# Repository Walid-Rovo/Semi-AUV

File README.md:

Welcome to the repository of Semi-AUV by Amgad Ehab, Walid Ismail. A Senior Project in the Arab Academy for Science & Technology under the supervision of Dr Shady A. Maged.

This repository will include all aspects of developing a semi-autonomous underwater vehicle for marine robotics research and educational purposes.

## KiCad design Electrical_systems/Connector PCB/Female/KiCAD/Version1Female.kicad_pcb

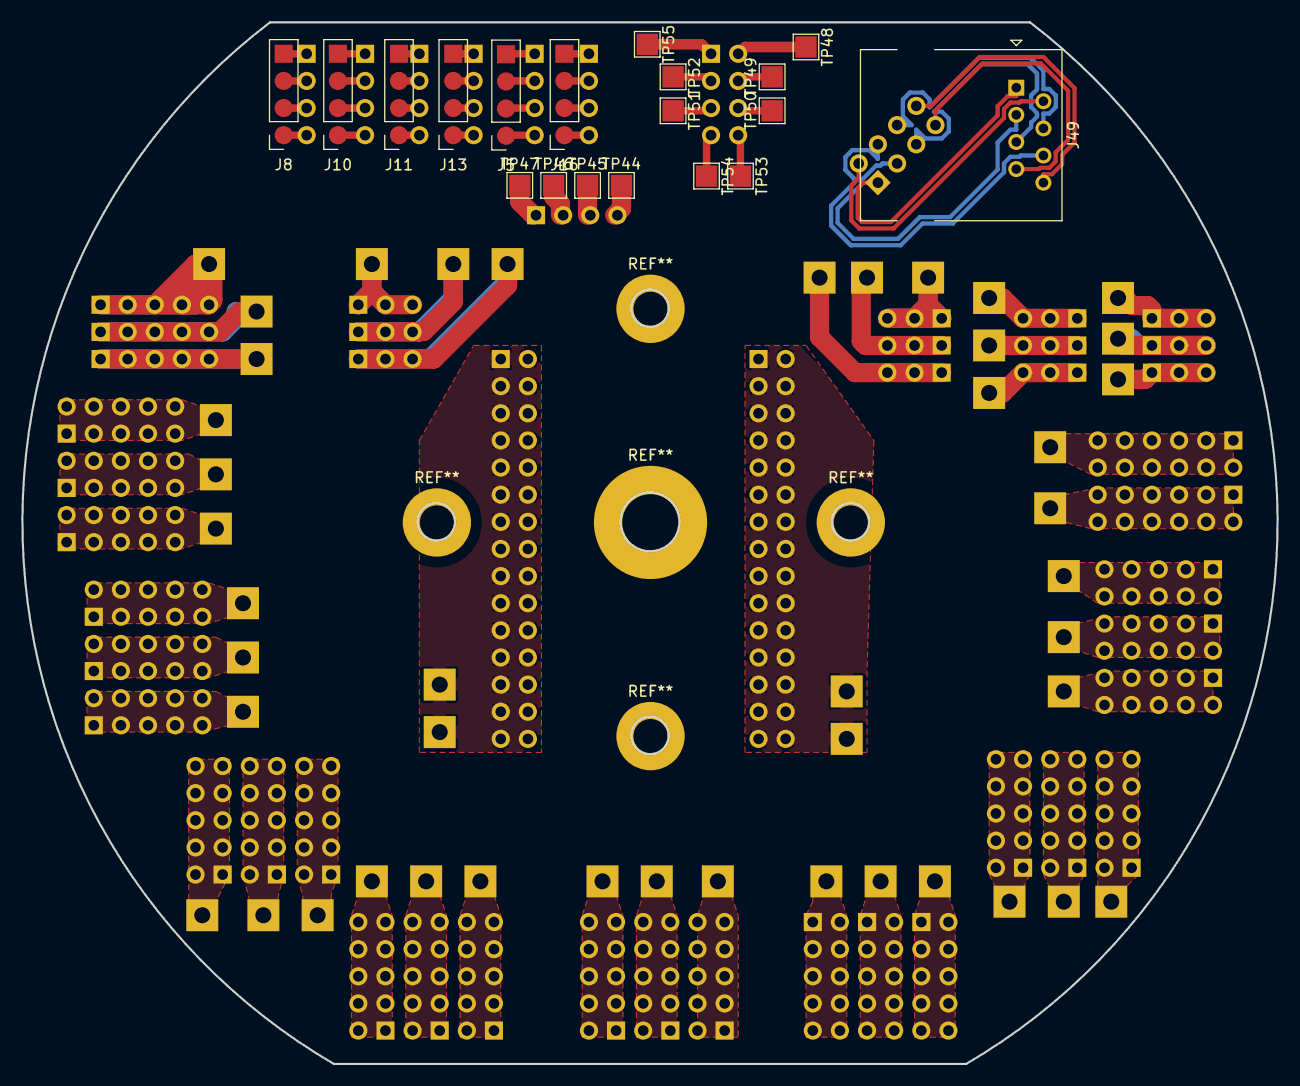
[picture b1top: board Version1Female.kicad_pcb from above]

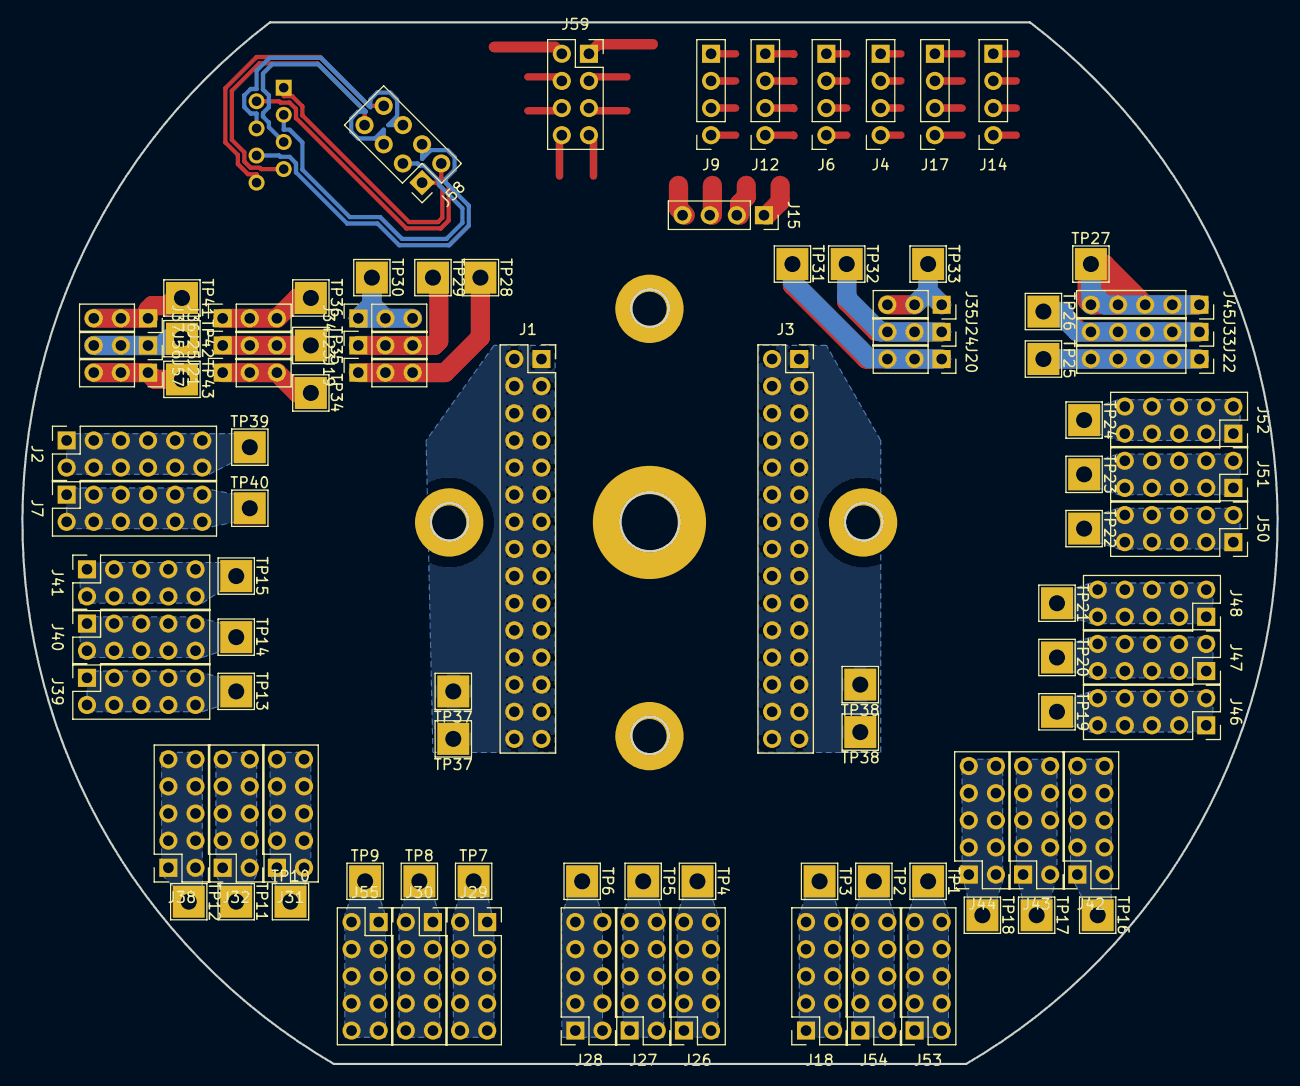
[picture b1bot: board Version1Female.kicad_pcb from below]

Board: 2 copper layers, 117.5 x 97.5 mm, 116 parts (97 on the bottom side), 79 nets.

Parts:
J1, J3: Conn_01x30_Male; PinSocket_2x15_P2.54mm_Vertical
J2, J7: Conn_01x12_Male; PinSocket_2x06_P2.54mm_Vertical
J4, J5, J6, J8, J9, J10, J11, J12, J13, J14, J16, J17: Conn_01x04; PinSocket_1x04_P2.54mm_Vertical
J15: Conn_01x04_Male; PinSocket_1x04_P2.54mm_Vertical
J18, J26, J27, J28, J29, J30, J31, J32, J38, J39, J40, J41, J42, J43, J44, J46, J47, J48, J50, J51, J52, J53, J54, J55: Conn_01x10; PinSocket_2x05_P2.54mm_Vertical
J19, J20, J21, J23, J24, J25, J34, J35, J36, J37, J56, J57: Conn_01x03_Male; PinSocket_1x03_P2.54mm_Vertical
J22, J33, J45: Conn_01x05_Male; PinSocket_1x05_P2.54mm_Vertical
J49: 8P8C; RJ45_Ninigi_GE
J58, J59: Conn_01x08; PinSocket_2x04_P2.54mm_Vertical
TP1, TP2, TP3, TP4, TP5, TP6, TP7, TP8, TP9, TP10, TP11, TP12, TP13, TP14, TP15, TP16, TP17, TP18, TP19, TP20, TP21, TP22, TP23, TP24, TP25, TP26, TP27, TP28, TP29, TP30, TP31, TP32, TP33, TP34, TP35, TP36, TP37, TP37#2, TP38, TP38#2, TP39, TP40, TP41, TP42, TP43: TestPoint; TestPoint_THTPad_3.0x3.0mm_Drill1.5mm
TP44, TP45, TP46, TP47, TP48, TP49, TP50, TP51, TP52, TP53, TP54, TP55: TestPoint; TestPoint_Pad_2.0x2.0mm

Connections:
3V3: J15.2, TP46.1
+12_VB1: J2.1, J2.2, J2.3, J2.4, J2.5, J2.6, J2.7, J2.8, J2.9, J2.10, J2.11, J2.12, TP39.1
+48_VA: J1.1, J1.2, J1.3, J1.4, J1.5, J1.6, J1.7, J1.8, J1.9, J1.10, J1.11, J1.12, J1.13, J1.14, J1.15, J1.16, J1.17, J1.18, J1.19, J1.20, J1.21, J1.22, J1.23, J1.24, J1.25, J1.26, J1.27, J1.28, J1.29, J1.30, TP37.1, TP37#2.1
+M0: J22.1, J22.2, J22.3, J22.4, J22.5, TP25.1
+M1: J19.1, J19.2, J19.3, TP28.1
+M2: J20.1, J20.2, J20.3, TP31.1
+M3: J21.1, J21.2, J21.3, TP34.1
+M4: J37.1, J37.2, J37.3, TP41.1
-M0: J33.1, J33.2, J33.3, J33.4, J33.5, TP26.1
-M1: J23.1, J23.2, J23.3, TP29.1
-M2: J24.1, J24.2, J24.3, TP32.1
-M3: J25.1, J25.2, J25.3, TP35.1
-M4: J56.1, J56.2, J56.3, TP42.1
EthA+: J49.2, J58.2
EthA-: J49.1, J58.1
EthB+: J49.6, J58.4
EthB-: J49.3, J58.3
EthC+: J49.5, J58.5
EthC-: J49.4, J58.6
EthD+: J49.8, J58.8
EthD-: J49.7, J58.7
GND: J15.1, TP47.1, TP55.1
GND_VA: J3.1, J3.2, J3.3, J3.4, J3.5, J3.6, J3.7, J3.8, J3.9, J3.10, J3.11, J3.12, J3.13, J3.14, J3.15, J3.16, J3.17, J3.18, J3.19, J3.20, J3.21, J3.22, J3.23, J3.24, J3.25, J3.26, J3.27, J3.28, J3.29, J3.30, TP38.1, TP38#2.1
GND_VB1: J7.1, J7.2, J7.3, J7.4, J7.5, J7.6, J7.7, J7.8, J7.9, J7.10, J7.11, J7.12, TP40.1
RA1: J4.1, J11.1
RA2: J4.2, J11.2
RA3: J4.3, J11.3
RA4: J4.4, J11.4
RB1: J5.1, J12.1
RB2: J5.2, J12.2
RB3: J5.3, J12.3
RB4: J5.4, J12.4
RC1: J6.1, J13.1
RC2: J6.2, J13.2
RC3: J6.3, J13.3
RC4: J6.4, J13.4
RD1: J8.1, J14.1
RD2: J8.2, J14.2
RD3: J8.3, J14.3
RD4: J8.4, J14.4
RE1: J9.1, J16.1
RE2: J9.2, J16.2
RE3: J9.3, J16.3
RE4: J9.4, J16.4
RF1: J10.1, J17.1
RF2: J10.2, J17.2
RF3: J10.3, J17.3
RF4: J10.4, J17.4
SCL: J15.4, TP44.1
SDA: J15.3, TP45.1
T0B: J18.1, J18.2, J18.3, J18.4, J18.5, J18.6, J18.7, J18.8, J18.9, J18.10, TP3.1
T0G: J54.1, J54.2, J54.3, J54.4, J54.5, J54.6, J54.7, J54.8, J54.9, J54.10, TP2.1
T0R: J53.1, J53.2, J53.3, J53.4, J53.5, J53.6, J53.7, J53.8, J53.9, J53.10, TP1.1
T1B: J28.1, J28.2, J28.3, J28.4, J28.5, J28.6, J28.7, J28.8, J28.9, J28.10, TP6.1
T1G: J27.1, J27.2, J27.3, J27.4, J27.5, J27.6, J27.7, J27.8, J27.9, J27.10, TP5.1
T1R: J26.1, J26.2, J26.3, J26.4, J26.5, J26.6, J26.7, J26.8, J26.9, J26.10, TP4.1
T2B: J55.1, J55.2, J55.3, J55.4, J55.5, J55.6, J55.7, J55.8, J55.9, J55.10, TP9.1
T2G: J30.1, J30.2, J30.3, J30.4, J30.5, J30.6, J30.7, J30.8, J30.9, J30.10, TP8.1
T2R: J29.1, J29.2, J29.3, J29.4, J29.5, J29.6, J29.7, J29.8, J29.9, J29.10, TP7.1
T3B: J38.1, J38.2, J38.3, J38.4, J38.5, J38.6, J38.7, J38.8, J38.9, J38.10, TP12.1
T3G: J32.1, J32.2, J32.3, J32.4, J32.5, J32.6, J32.7, J32.8, J32.9, J32.10, TP11.1
T3R: J31.1, J31.2, J31.3, J31.4, J31.5, J31.6, J31.7, J31.8, J31.9, J31.10, TP10.1
T4B: J41.1, J41.2, J41.3, J41.4, J41.5, J41.6, J41.7, J41.8, J41.9, J41.10, TP15.1
T4G: J40.1, J40.2, J40.3, J40.4, J40.5, J40.6, J40.7, J40.8, J40.9, J40.10, TP14.1
T4R: J39.1, J39.2, J39.3, J39.4, J39.5, J39.6, J39.7, J39.8, J39.9, J39.10, TP13.1
T5B: J44.1, J44.2, J44.3, J44.4, J44.5, J44.6, J44.7, J44.8, J44.9, J44.10, TP18.1
T5G: J43.1, J43.2, J43.3, J43.4, J43.5, J43.6, J43.7, J43.8, J43.9, J43.10, TP17.1
T5R: J42.1, J42.2, J42.3, J42.4, J42.5, J42.6, J42.7, J42.8, J42.9, J42.10, TP16.1
T6B: J48.1, J48.2, J48.3, J48.4, J48.5, J48.6, J48.7, J48.8, J48.9, J48.10, TP21.1
T6G: J47.1, J47.2, J47.3, J47.4, J47.5, J47.6, J47.7, J47.8, J47.9, J47.10, TP20.1
T6R: J46.1, J46.2, J46.3, J46.4, J46.5, J46.6, J46.7, J46.8, J46.9, J46.10, TP19.1
T7B: J52.1, J52.2, J52.3, J52.4, J52.5, J52.6, J52.7, J52.8, J52.9, J52.10, TP24.1
T7G: J51.1, J51.2, J51.3, J51.4, J51.5, J51.6, J51.7, J51.8, J51.9, J51.10, TP23.1
T7R: J50.1, J50.2, J50.3, J50.4, J50.5, J50.6, J50.7, J50.8, J50.9, J50.10, TP22.1
XM0: J45.1, J45.2, J45.3, J45.4, J45.5, TP27.1
XM1: J34.1, J34.2, J34.3, TP30.1
XM2: J35.1, J35.2, J35.3, TP33.1
XM3: J36.1, J36.2, J36.3, TP36.1
XM4: J57.1, J57.2, J57.3, TP43.1

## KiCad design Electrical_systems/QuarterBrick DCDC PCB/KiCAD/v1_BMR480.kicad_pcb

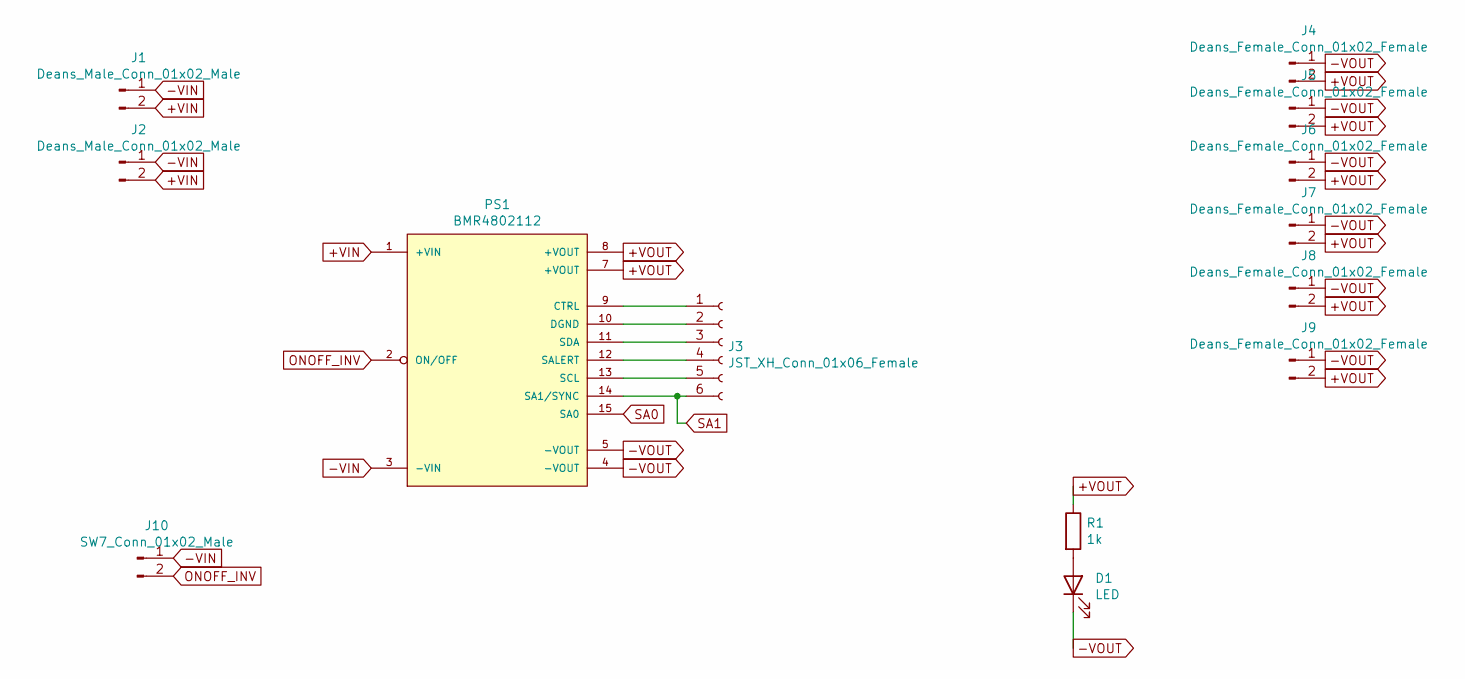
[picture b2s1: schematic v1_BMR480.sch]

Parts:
D1: LED; LED_D1.8mm_W3.3mm_H2.4mm
J1, J2: Deans_Male_Conn_01x02_Male; DeansPlug_Male
J3: JST_XH_Conn_01x06_Female; JST_XH_B6B-XH-A_1x06_P2.50mm_Vertical
J4, J5, J6, J7, J8, J9: Deans_Female_Conn_01x02_Female; DeansPlug_Female
J10: SW7_Conn_01x02_Male; PinSocket_1x03_P2.54mm_Vertical
PS1: BMR4802112; BMR480-QuarterBrick_PMBus
R1: 1k; R_Axial_DIN0204_L3.6mm_D1.6mm_P5.08mm_Horizontal

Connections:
+VIN: J1.2, J2.2, PS1.1 (+VIN)
+VOUT: J4.2, J5.2, J6.2, J7.2, J8.2, J9.2, PS1.7 (+VOUT), PS1.8 (+VOUT), R1.1
-VIN: J1.1, J2.1, J10.1, PS1.3 (-VIN)
-VOUT: D1.1 (K), J4.1, J5.1, J6.1, J7.1, J8.1, J9.1, PS1.4 (-VOUT), PS1.5 (-VOUT)
unnamed: D1.2 (A), R1.2
unnamed: J3.1, PS1.9 (CTRL)
unnamed: J3.2, PS1.10 (DGND)
unnamed: J3.3, PS1.11 (SDA)
unnamed: J3.4, PS1.12 (SALERT)
unnamed: J3.5, PS1.13 (SCL)
ONOFF_INV: J10.2, PS1.2 (ON/OFF)
SA0: PS1.15 (SA0)
SA1: J3.6, PS1.14 (SA1/SYNC)

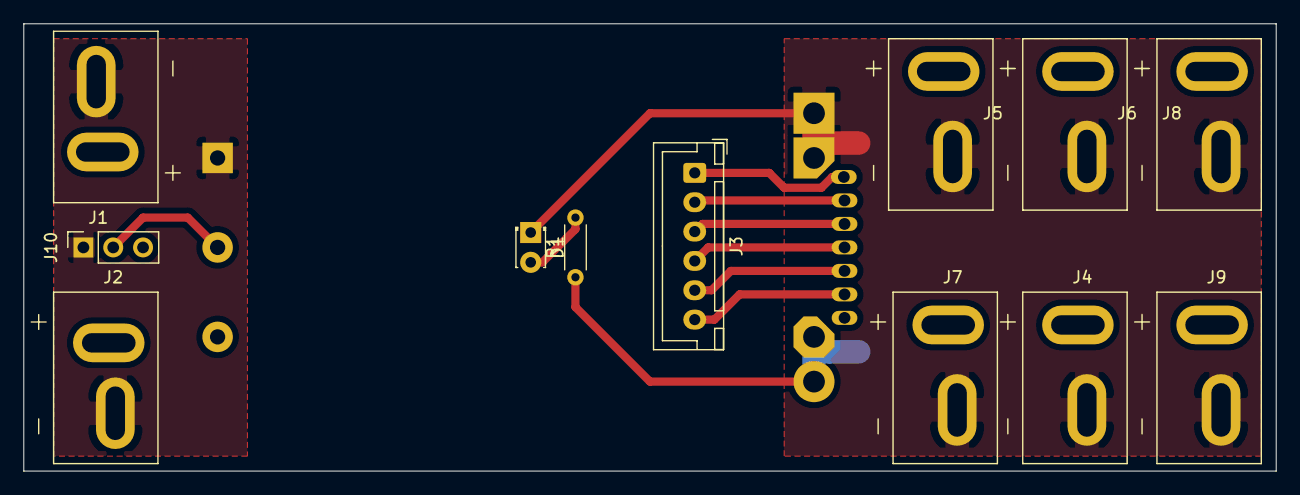
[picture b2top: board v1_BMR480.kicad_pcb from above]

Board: 2 copper layers, 106.7 x 38.1 mm, 13 parts (1 on the bottom side), 12 nets.

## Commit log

2021-03-14 figures
2021-03-14 Added figures, cleaned up abstracts, changed HUWV to Semi-AUV
2021-03-14 vr added
2021-07-03 Added mechanical systems body, tube, rack. Added electrical systems DCDC PCB, connector PCB. Added software outline.
2021-07-03 Add body, tube, rack.
2021-07-03 Add body as STEP
    Unable to upload SolidWorks files.
